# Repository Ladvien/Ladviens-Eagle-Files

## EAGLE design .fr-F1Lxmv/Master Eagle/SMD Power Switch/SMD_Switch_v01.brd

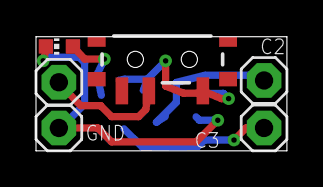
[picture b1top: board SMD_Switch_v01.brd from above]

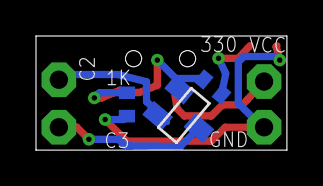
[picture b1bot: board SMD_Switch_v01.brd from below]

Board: 2 copper layers, 13.9 x 6.3 mm, 9 parts (3 on the bottom side), 6 nets.

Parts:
JP1, JP2, JP3, JP4: 1X01
LED1: CHIP-LED0603
Q1: MOSFET-NCHANNELBSS123LT1G; SOT23
R1: 330; R0402
R2: 1k; R0402
S1: SWITCH-SPST-SMD-A

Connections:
C2: JP1.1, Q1.2
C3: JP2.1, Q1.3
GND: JP4.1, LED1.C, R2.2
unnamed: LED1.A, R1.1
unnamed: Q1.1, R1.2, R2.1, S1.3
VCC: JP3.1, S1.2

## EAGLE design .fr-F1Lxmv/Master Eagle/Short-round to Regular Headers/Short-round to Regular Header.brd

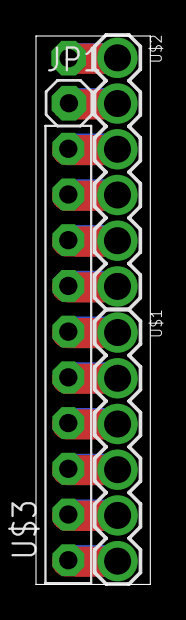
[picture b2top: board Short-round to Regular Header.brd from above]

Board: 2 copper layers, 6.3 x 30.5 mm, 5 parts (1 on the bottom side), 12 nets.

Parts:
JP1, JP2: 1X01
U$1, U$2: 1X6_SHORT_ROUND
U$3: PINHD-1X10; 1X10-BIG

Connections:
unnamed: U$1.6, U$3.1
unnamed: U$1.5, U$3.2
unnamed: U$1.4, U$3.3
unnamed: U$1.3, U$3.4
unnamed: U$1.2, U$3.5
unnamed: U$1.1, U$3.6
unnamed: U$2.6, U$3.7
unnamed: U$2.5, U$3.8
unnamed: U$2.4, U$3.9
unnamed: U$2.3, U$3.10
unnamed: JP1.1, U$2.2
unnamed: JP2.1, U$2.1

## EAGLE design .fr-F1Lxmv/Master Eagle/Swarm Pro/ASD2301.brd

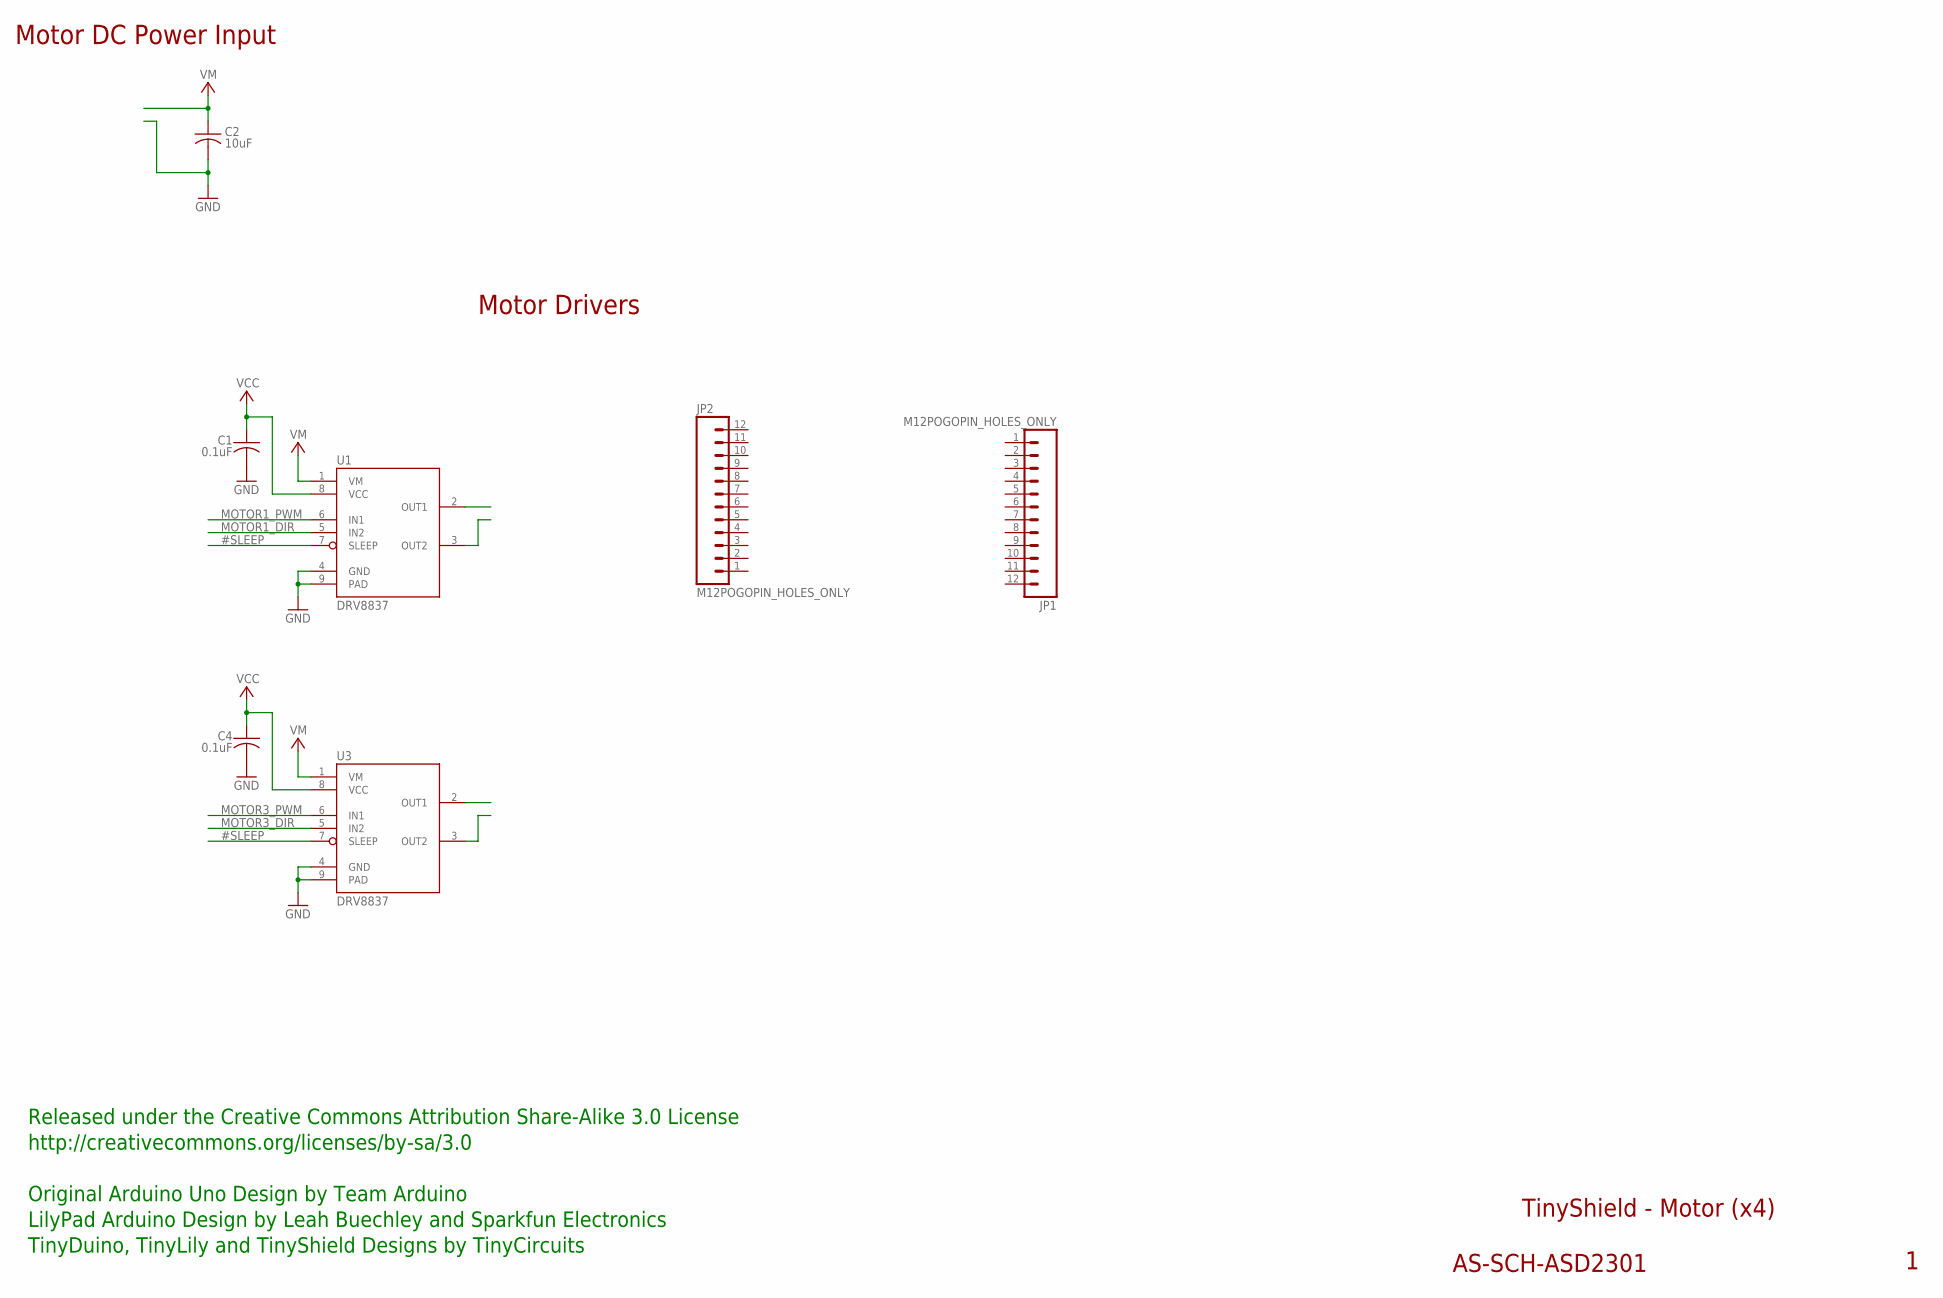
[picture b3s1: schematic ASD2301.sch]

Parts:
C1, C4: 0.1uF; C0402
C2: 10uF; C0805
JP1, JP2: M12POGOPIN_HOLES_ONLY; 1X12_HOLES_ONLY
U1, U3: DRV8837; WSON-8

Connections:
#SLEEP: U1.7 (SLEEP), U3.7 (SLEEP)
GND: C1.2, C2.2, C4.2, U1.4 (GND), U1.9 (PAD), U3.4 (GND), U3.9 (PAD)
MOTOR1_DIR: U1.5 (IN2)
MOTOR1_PWM: U1.6 (IN1)
MOTOR3_DIR: U3.5 (IN2)
MOTOR3_PWM: U3.6 (IN1)
VCC: C1.1, C4.1, U1.8 (VCC), U3.8 (VCC)
VM: C2.1, U1.1 (VM), U3.1 (VM)

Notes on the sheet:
TinyShield - Motor (x4)
AS-SCH-ASD2301
Released under the Creative Commons Attribution Share-Alike 3.0 License
http://creativecommons.org/licenses/by-sa/3.0
LilyPad Arduino Design by Leah Buechley and Sparkfun Electronics
TinyDuino, TinyLily and TinyShield Designs by TinyCircuits
Original Arduino Uno Design by Team Arduino
Motor Drivers
Motor DC Power Input

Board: 2 copper layers, 7 parts (0 on the bottom side), 4 nets, no tracks yet.

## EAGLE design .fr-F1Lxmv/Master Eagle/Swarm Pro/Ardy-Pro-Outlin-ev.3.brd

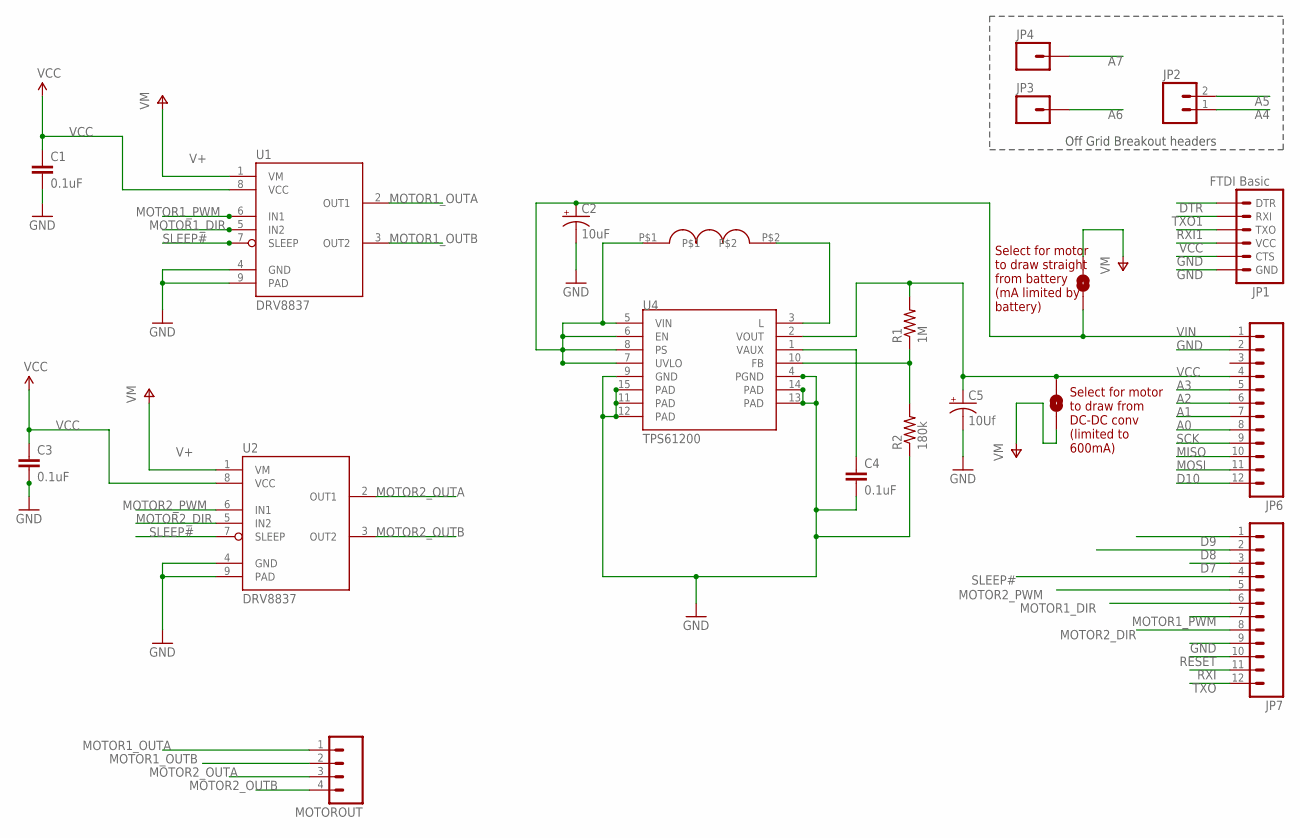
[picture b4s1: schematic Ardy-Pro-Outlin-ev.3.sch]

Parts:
2.2UH: 2.2uh; PEBBLE_VLF4012A
C1, C3, C4: 0.1uF; 0805
C2: 10uF; EIA3216
C5: 10Uf; EIA3216
JP1: FTDI Basic; 1X06
JP2: M02PTH; 1X02
JP3, JP4: M01PTH; 1X01
JP6, JP7: M12PTH; 1X12
MOTOROUT: M04PTH; 1X04
R1: 1M; 0805
R2: 180k; 0805
SJ1, SJ2: SOLDERJUMPERNO; SJ_2S-NO
U1, U2: DRV8837; WSON-8
U4: TPS61200; QFN-10_PAD

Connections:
A0: JP6.8
A1: JP6.7
A2: JP6.6
A3: JP6.5
A4: JP2.1
A5: JP2.2
A6: JP3.1
A7: JP4.1
D7: JP7.3
D8: JP7.2
D9: JP7.1
D10: JP6.12
DTR: JP1.1 (DTR)
GND: C1.2, C2.C (-), C3.2, C4.2, C5.C (-), JP1.5 (CTS), JP1.6 (GND), JP6.2, JP7.9, R2.1, U1.4 (GND), U1.9 (PAD), U2.4 (GND), U2.9 (PAD), U4.4 (PGND), U4.9 (GND), U4.11 (PAD), U4.12 (PAD), U4.13 (PAD), U4.14 (PAD), U4.15 (PAD)
MISO: JP6.10
MOSI: JP6.11
MOTOR1_DIR: JP7.6, U1.5 (IN2)
MOTOR1_OUTA: MOTOROUT.1, U1.2 (OUT1)
MOTOR1_OUTB: MOTOROUT.2, U1.3 (OUT2)
MOTOR1_PWM: JP7.7, U1.6 (IN1)
MOTOR2_DIR: JP7.8, U2.5 (IN2)
MOTOR2_OUTA: MOTOROUT.3, U2.2 (OUT1)
MOTOR2_OUTB: MOTOROUT.4, U2.3 (OUT2)
MOTOR2_PWM: JP7.5, U2.6 (IN1)
unnamed: 2.2UH.P$2, U4.3 (L)
unnamed: C4.1, U4.1 (VAUX)
unnamed: R1.1, R2.2, U4.10 (FB)
RESET: JP7.10
RXI: JP7.11
RXI1: JP1.3 (TXO)
SCK: JP6.9
SLEEP#: JP7.4, U1.7 (SLEEP), U2.7 (SLEEP)
TXO: JP7.12
TXO1: JP1.2 (RXI)
V+: SJ1.1, SJ2.2, U1.1 (VM), U2.1 (VM)
VCC: C1.1, C3.1, C5.A (+), JP1.4 (VCC), JP6.4, R1.2, SJ1.2, U1.8 (VCC), U2.8 (VCC), U4.2 (VOUT)
VIN: 2.2UH.P$1, C2.A (+), JP6.1, SJ2.1, U4.5 (VIN), U4.6 (EN), U4.7 (UVLO), U4.8 (PS)

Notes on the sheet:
Off Grid Breakout headers
Select for motor to draw straight from battery (mA limited by battery)
Select for motor to draw from DC-DC conv (limited to 600mA)

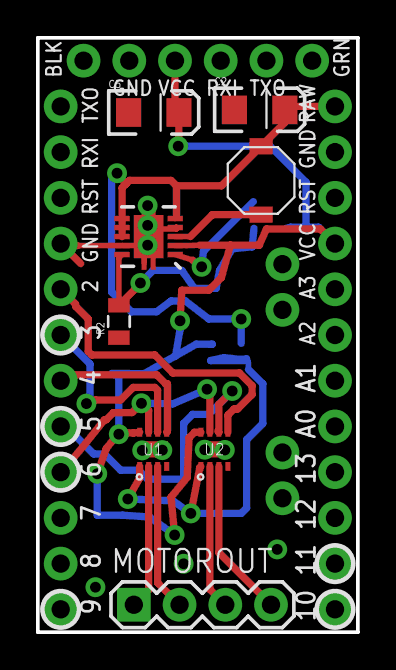
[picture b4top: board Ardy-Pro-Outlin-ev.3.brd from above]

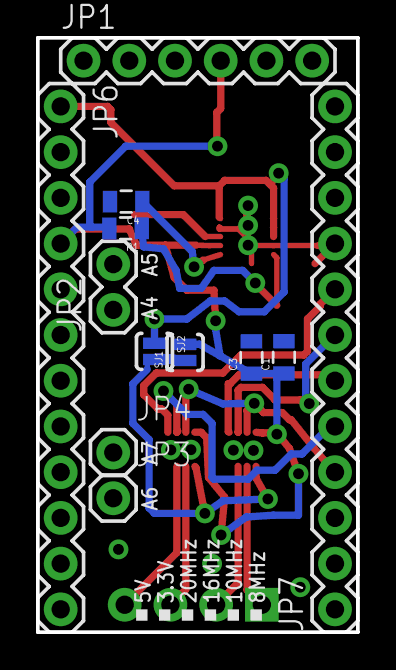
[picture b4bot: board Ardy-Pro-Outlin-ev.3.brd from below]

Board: 2 copper layers, 17.8 x 33.0 mm, 20 parts (12 on the bottom side), 16 nets.

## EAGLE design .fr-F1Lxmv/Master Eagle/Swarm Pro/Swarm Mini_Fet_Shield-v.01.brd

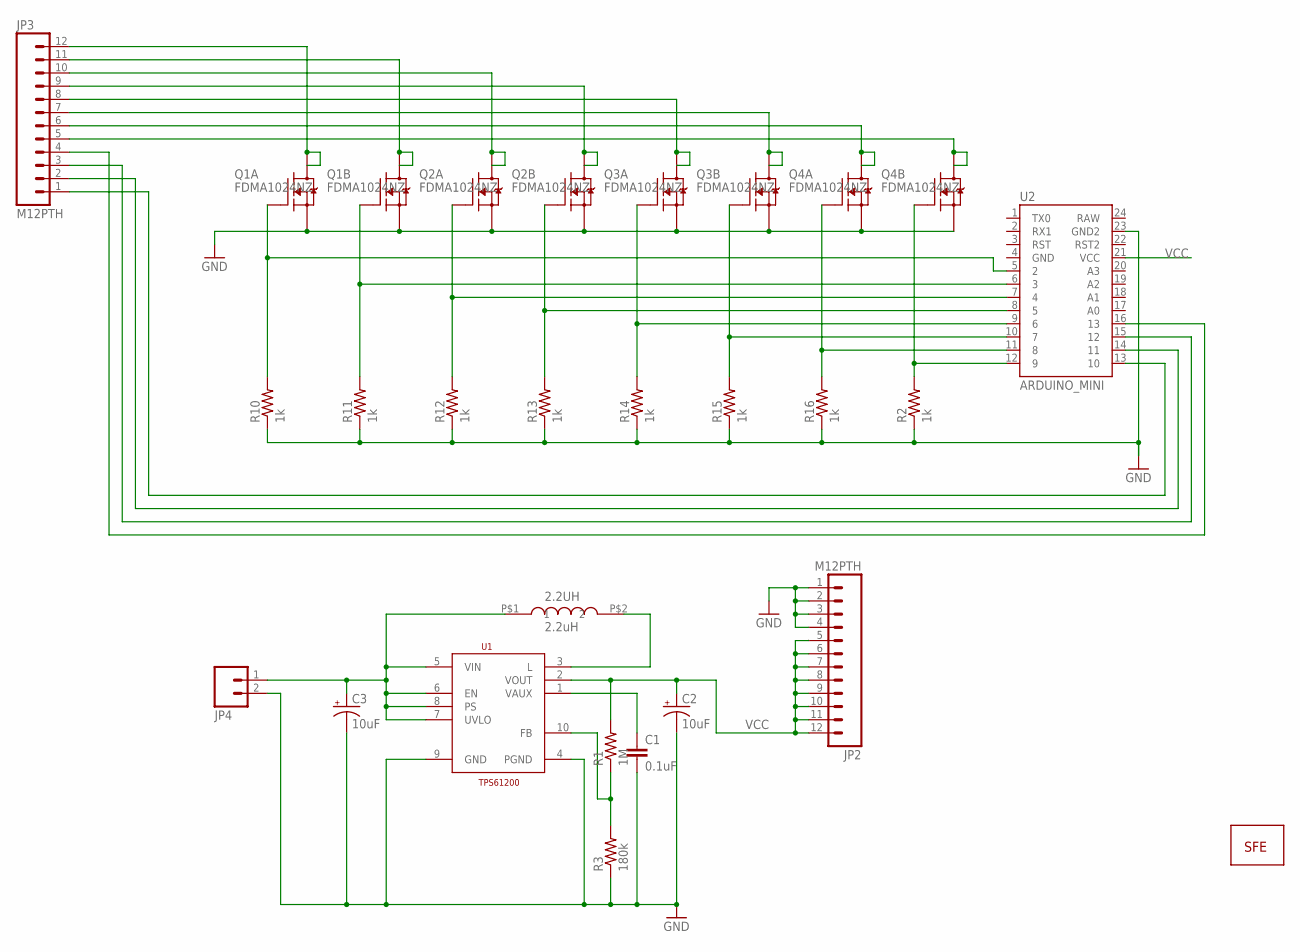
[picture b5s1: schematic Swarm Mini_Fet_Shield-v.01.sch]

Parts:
2.2UH: 2.2uH; VLF4012A
C1: 0.1uF; 0805
C2, C3: 10uF; EIA3216
JP2, JP3: M12PTH; 1X12
JP4: M02PTH; 1X02
JP5: LOGO-SFESK; SFE-LOGO-FLAME
Q1, Q2, Q3, Q4: FDMA1024NZ; MICROFET_2X2
R1: 1M; 0805
R2, R10, R11, R12, R13, R14, R15, R16: 1k; 0805
R3: 180k; 0402-RES
U1: TPS61200; DRC-S-PVSON-N10
U2: ARDUINO_MINI

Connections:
GND: C1.2, C2.C (-), C3.C (-), JP2.1, JP2.2, JP2.3, JP2.4, JP4.2, Q1.S1 (S), Q1.S2 (S), Q2.S1 (S), Q2.S2 (S), Q3.S1 (S), Q3.S2 (S), Q4.S1 (S), Q4.S2 (S), R2.1, R3.1, R10.1, R11.1, R12.1, R13.1, R14.1, R15.1, R16.1, U1.4 (PGND), U1.9 (GND), U2.23 (GND2)
unnamed: JP3.4, U2.16 (13)
unnamed: R1.1, R3.2, U1.10 (FB)
unnamed: C1.1, U1.1 (VAUX)
unnamed: 2.2UH.P$2 (2), U1.3 (L)
unnamed: Q1.G1 (G), R10.2, U2.5 (2)
unnamed: 2.2UH.P$1 (1), C3.A (+), JP4.1, U1.5 (VIN), U1.6 (EN), U1.7 (UVLO), U1.8 (PS)
unnamed: Q1.G2 (G), R11.2, U2.6 (3)
unnamed: Q2.G1 (G), R12.2, U2.7 (4)
unnamed: Q2.G2 (G), R13.2, U2.8 (5)
unnamed: Q3.G1 (G), R14.2, U2.9 (6)
unnamed: Q3.G2 (G), R15.2, U2.10 (7)
unnamed: Q4.G1 (G), R16.2, U2.11 (8)
unnamed: Q4.G2 (G), R2.2, U2.12 (9)
unnamed: JP3.12, Q1.D1 (D), Q1.D1_2 (D1)
unnamed: JP3.11, Q1.D2 (D), Q1.D2_2 (D1)
unnamed: JP3.10, Q2.D1 (D), Q2.D1_2 (D1)
unnamed: JP3.9, Q2.D2 (D), Q2.D2_2 (D1)
unnamed: JP3.8, Q3.D1 (D), Q3.D1_2 (D1)
unnamed: JP3.7, Q3.D2 (D), Q3.D2_2 (D1)
unnamed: JP3.6, Q4.D1 (D), Q4.D1_2 (D1)
unnamed: JP3.5, Q4.D2 (D), Q4.D2_2 (D1)
unnamed: JP3.3, U2.15 (12)
unnamed: JP3.2, U2.14 (11)
unnamed: JP3.1, U2.13 (10)
VCC: C2.A (+), JP2.5, JP2.6, JP2.7, JP2.8, JP2.9, JP2.10, JP2.11, JP2.12, R1.2, U1.2 (VOUT), U2.21 (VCC)

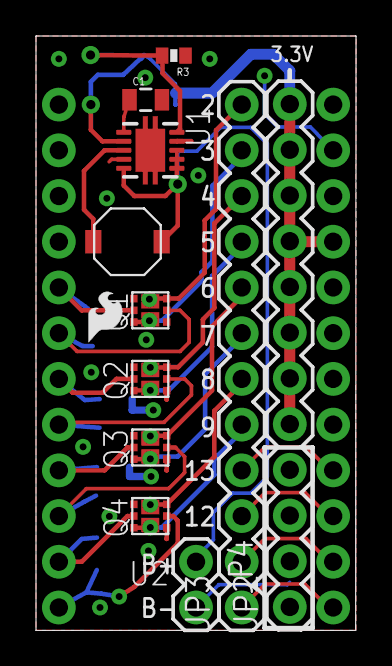
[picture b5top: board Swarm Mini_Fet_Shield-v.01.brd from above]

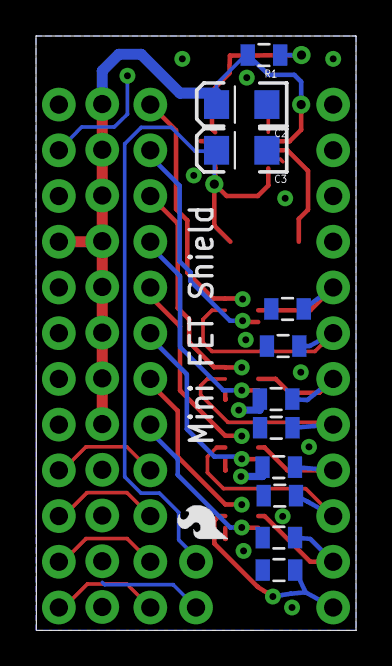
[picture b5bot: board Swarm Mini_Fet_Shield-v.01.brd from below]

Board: 2 copper layers, 17.8 x 33.0 mm, 25 parts (12 on the bottom side), 26 nets.

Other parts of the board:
JP1: LOGO-SFESK; SFE-LOGO-FLAME

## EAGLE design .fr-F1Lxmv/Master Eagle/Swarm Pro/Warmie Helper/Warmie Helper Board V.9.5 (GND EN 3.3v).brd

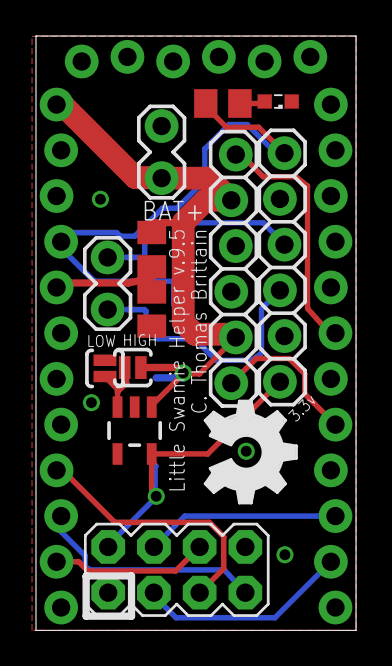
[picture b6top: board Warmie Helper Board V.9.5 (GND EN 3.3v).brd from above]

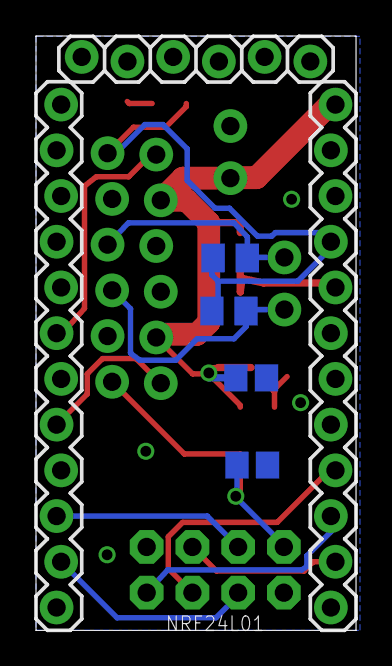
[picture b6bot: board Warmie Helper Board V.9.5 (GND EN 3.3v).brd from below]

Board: 2 copper layers, 17.8 x 33.0 mm, 20 parts (7 on the bottom side), 16 nets.

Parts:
BATTERY: 1X02_LOCK
C1, C2: 1uF; C0805
JP1, JP2: M12LOCK; 1X12_LOCK
JP5: 1X02_LOCK
JP6, JP8, JP9: 1X06_LOCK
LED1: SML0603
NRF24L01: M04X2; 2X4
R1, R2: 4.7k; M0805
R3, R4, R5: 330; M0805
SJ1, SJ2: SOLDERJUMPERNO; SJ_2S-NO
U1: AAT3221/22; SOT23-5
U$2: OSHW_FILLX200_NOTEXT

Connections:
5V: JP1.9, JP9.1, R1.1, R2.1, R3.2
A3: JP1.8, R4.2, R5.1
A4: JP5.1, JP9.4, R1.2
A5: JP5.2, JP9.3, R2.2
CE: JP2.2, NRF24L01.6
CSN: JP2.3, NRF24L01.5
D3: JP2.7, JP8.6
D5: JP2.5, JP8.1
GND: BATTERY.2, C1.2, C2.2, JP1.11, JP2.9, JP6.1, JP6.2, JP8.3, JP8.4, JP9.2, LED1.C, NRF24L01.8, R5.2, SJ2.1, U1.2
MISO: JP1.3, NRF24L01.2
MOSI: JP1.2, NRF24L01.3
unnamed: SJ1.1, SJ2.2, U1.3
unnamed: LED1.A, R3.1
SCK: JP1.4, NRF24L01.4
V3.3: C1.1, JP9.6, NRF24L01.7, U1.5
VIN: BATTERY.1, C2.1, JP1.12, JP8.2, JP8.5, R4.1, SJ1.2, U1.1

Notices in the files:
parts and their libraries:
SparkFun-Electromechanical: Licensing: CC v3.0 Share-Alike You are welcome to use this library for commercial purposes.
